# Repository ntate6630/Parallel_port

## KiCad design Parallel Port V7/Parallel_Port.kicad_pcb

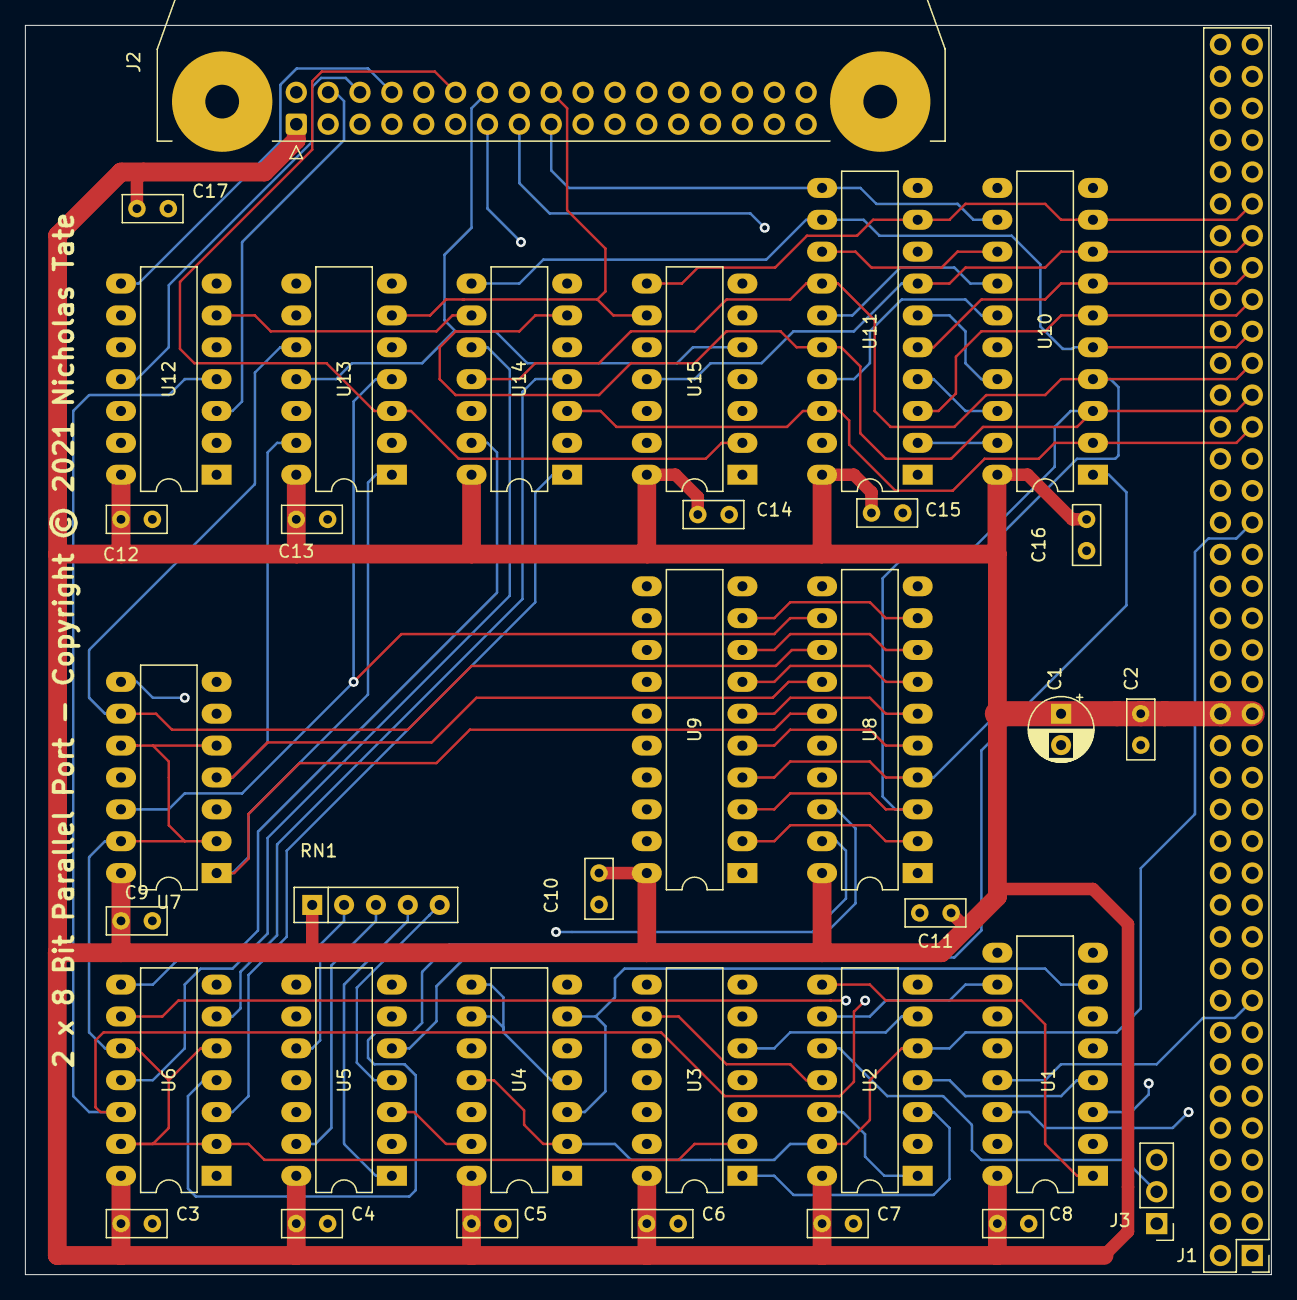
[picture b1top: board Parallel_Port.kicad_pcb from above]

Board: 4 copper layers, 99.3 x 99.6 mm, 36 parts (0 on the bottom side), 81 nets.

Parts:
C1: 100uF; CP_Radial_D5.0mm_P2.50mm
C2, C3, C4, C5, C6, C7, C8, C9, C10, C11, C12, C13, C14, C15, C16, C17: 0.1uF; C_Rect_L4.6mm_W2.0mm_P2.50mm_MKS02_FKP02
J1: Conn_02x39_Odd_Even; PinHeader_2x39_P2.54mm_Vertical
J2: Conn_02x17_Odd_Even; IDC-Header_2x17-1MP_P2.54mm_Latch_Horizontal
J3: Conn_01x03; PinHeader_1x03_P2.54mm_Vertical
RN1: 10k; R_Array_SIP5
U1: 74F139; DIP-16_W7.62mm_LongPads
U2: 74F32; DIP-14_W7.62mm_LongPads
U3: 74F14; DIP-14_W7.62mm_LongPads
U4: 74F02; DIP-14_W7.62mm_LongPads
U5: 74F74; DIP-14_W7.62mm_LongPads
U6, U7: 74F00; DIP-14_W7.62mm_LongPads
U8, U9, U10: 74F573; DIP-20_W7.62mm_LongPads
U11: 74F244; DIP-20_W7.62mm_LongPads
U12, U13, U14, U15: 74F125; DIP-14_W7.62mm_LongPads

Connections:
+5V: C1.1, C2.1, C3.1, C4.1, C5.1, C6.1, C7.1, C8.1, C9.1, C10.1, C11.1, C12.1, C13.1, C14.1, C15.1, C16.1, C17.1, J1.35, J1.36, J2.1, RN1.1, U1.16, U2.14, U3.14, U4.14, U5.14, U6.14, U7.14, U8.20, U9.20, U10.20, U11.20, U12.14, U13.14, U14.14, U15.14
/A0: J1.31, U1.2
/A1: J1.29, U1.3
/A2: J1.27, J3.3, U3.3
/A6: J1.19, U1.14
/A7: J1.17, U1.13
/BDC0: U6.3, U14.1
/BDC1: U6.6, U14.4
/BDC2: U6.8, U14.13
/BDC3: U6.11, U14.10
/BDC4: U7.3, U15.1
/BDC5: U7.6, U15.4
/BDC6: U7.8, U15.13
/BDC7: U7.11, U15.10
/CE_80: U1.4, U2.4
/CE_81: U1.5, U2.1, U2.12
/CE_82A: U1.6, U4.12
/CE_82B: U4.13, U5.3
/CE_83A: U1.7, U4.3, U4.6
/CE_83B: U4.1, U10.11
/CE_83C: U4.10, U11.1, U11.19
/D0: J1.53, U5.2, U8.2, U9.2, U10.2, U11.18, U14.3
/D1: J1.55, U8.3, U9.3, U10.3, U11.16, U14.6
/D2: J1.57, U8.4, U9.4, U10.4, U11.14, U14.11
/D3: J1.59, U8.5, U9.5, U10.5, U11.12, U14.8
/D4: J1.61, U8.6, U9.6, U10.6, U11.3, U15.3
/D5: J1.63, U8.7, U9.7, U10.7, U11.5, U15.6
/D6: J1.65, U8.8, U9.8, U10.8, U11.7, U15.11
/D7: J1.67, U8.9, U9.9, U10.9, U11.9, U15.8
/IORQ: J1.51, U1.15
/PA0: J2.3, U10.19, U11.2
/PA1: J2.5, U10.18, U11.4
/PA2: J2.7, U10.17, U11.6
/PA3: J2.9, U10.16, U11.8
/PA4: J2.11, U10.15, U11.17
/PA5: J2.13, U10.14, U11.15
/PA6: J2.15, U10.13, U11.13
/PA7: J2.17, U10.12, U11.11
/PB0: J2.4, U12.3, U14.2
/PB1: J2.6, U12.11, U14.5
/PB2: J2.8, U12.8, U14.12
/PB3: J2.10, U12.6, U14.9
/PB4: J2.12, U13.3, U15.2
/PB5: J2.14, U13.11, U15.5
/PB6: J2.16, U13.8, U15.12
/PB7: J2.18, U13.6, U15.9
/PDB0: U6.1, U8.19, U12.1
/PDB1: U6.4, U8.18, U12.13
/PDB2: U6.9, U8.17, U12.10
/PDB3: U6.12, U8.16, U12.4
/PDB4: U7.1, U8.15, U13.1
/PDB5: U7.4, U8.14, U13.13
/PDB6: U7.9, U8.13, U13.10
/PDB7: U7.12, U8.12, U13.4
/RD: J1.49, U2.2, U4.5
/WR: J1.47, U2.5, U2.13, U4.2, U4.11
GND: C1.2, C2.2, C3.2, C4.2, C5.2, C6.2, C7.2, C8.2, C9.2, C10.2, C11.2, C12.2, C13.2, C14.2, C15.2, C16.2, C17.2, J1.33, J1.34, J2.33, U1.8, U2.7, U3.7, U3.11, U3.13, U4.7, U5.7, U5.11, U5.12, U6.7, U7.7, U8.1, U8.10, U9.1, U9.10, U10.10, U11.10, U12.7, U13.7, U14.7, U15.7
unnamed: J3.1, U3.4
unnamed: J3.2, U2.10
unnamed: RN1.2, U5.10
unnamed: RN1.3, U5.13
unnamed: RN1.4, U5.1
unnamed: RN1.5, U5.4
unnamed: U1.1, U2.8
unnamed: U1.10, U2.9
unnamed: U2.3, U3.1
unnamed: U2.6, U3.5
unnamed: U2.11, U3.9
unnamed: U3.2, U6.2, U6.5, U6.10, U6.13, U7.2, U7.5, U7.10, U7.13
unnamed: U3.6, U8.11
unnamed: U3.8, U9.11
unnamed: U4.4, U4.8, U4.9
unnamed: U5.5, U10.1
unnamed: U9.19, U12.2
unnamed: U9.16, U12.5
unnamed: U9.17, U12.9
unnamed: U9.18, U12.12
unnamed: U9.15, U13.2
unnamed: U9.12, U13.5
unnamed: U9.13, U13.9
unnamed: U9.14, U13.12

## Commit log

2022-03-21 Add files via upload
    First commit
2022-03-22 Add files via upload
    Users guide
2022-04-05 Add files via upload
    Font size changed
2022-04-12 Add files via upload
    Amendments and additions

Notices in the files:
Parallel Port V7/Parallel_Port.kicad_pcb:
2 x 8 Bit Parallel Port - Copyright © 2021 Nicholas Tate
